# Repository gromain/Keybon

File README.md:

# Keybon - Adaptive Macro Keyboard

Keybon is a macro keyboard with configurable layouts and functions. Integrated into each of its nine tactile buttons is a 0.66” OLED screen. Depending on which app is active on the connected computer, Keybon switches to the suitable key layout thanks to its companion software.

This repository also contains a 12 buttons version called Keybon12. The corresponding files and code were designed by Romain Bazile. It's built upon the work of [CoretechR](https://github.com/CoretechR/Keybon/).

# Instructions

1.  Download the USB bootloader: https://github.com/rogerclarkmelbourne/STM32duino-bootloader

    Connect a USB-to-Serial adapter to the TX/RX pins of your board. Close the BOOT0 jumper before applying power.

    Locate the file to flash, in the folder `bootloader_only_binaries/generic_boot20_pc13.bin`.

    Flash the USB bootloader to the STM32 via the STM32 flasher:  https://www.st.com/en/development-tools/flasher-stm32.html

    You can also use the `stm32loader.py` script provided by `STM32duino-bootloader` team.

    Do not forget to remove the BOOT0 jumper once you're done.

2.  Install the required Arduino libraries listed in the `keybon12.ino` file

    Important: **Adafruit_GFX_Library version 1.7.5** must be installed (dependencies for newer versions are incompatible with the STM32)

    Add these lines to the file `Adafruit_SSD1306.c` (in `Arduino/libraries/Adafruit_SSD1306`)
    
    ```C++
    } else if ((WIDTH == 128) && (HEIGHT == 48)) {
    comPins = 0x12;
	  contrast = (vccstate == SSD1306_EXTERNALVCC) ? 0x9F : 0xCF;
    ```

    They should be added around line 563, right after this:
    ```C++
    } else if ((WIDTH == 96) && (HEIGHT == 16)) {
    comPins = 0x2; // ada x12
    contrast = (vccstate == SSD1306_EXTERNALVCC) ? 0x10 : 0xAF;
    ```

3.  Install STM32 support for the Arduino IDE: https://github.com/rogerclarkmelbourne/Arduino_STM32

    Install the corresponding drivers: https://github.com/rogerclarkmelbourne/Arduino_STM32/tree/master/drivers

4.  Compile and upload the Arduino sketch:

    The first time you do this, you will need to short the BOOT1 jumper and then restart your Keybon (either by plugging it in, or by clicking on the reset button).

    If you are using Linux, you may need to add a udev rule to your system (or to use `sudo` with the last command executed by the Arduino IDE).

    If you need to create new icons for your display, you can use the tool at https://javl.github.io/image2cpp/ with png images, in black and white only and a resolution of 64*48 pixels.

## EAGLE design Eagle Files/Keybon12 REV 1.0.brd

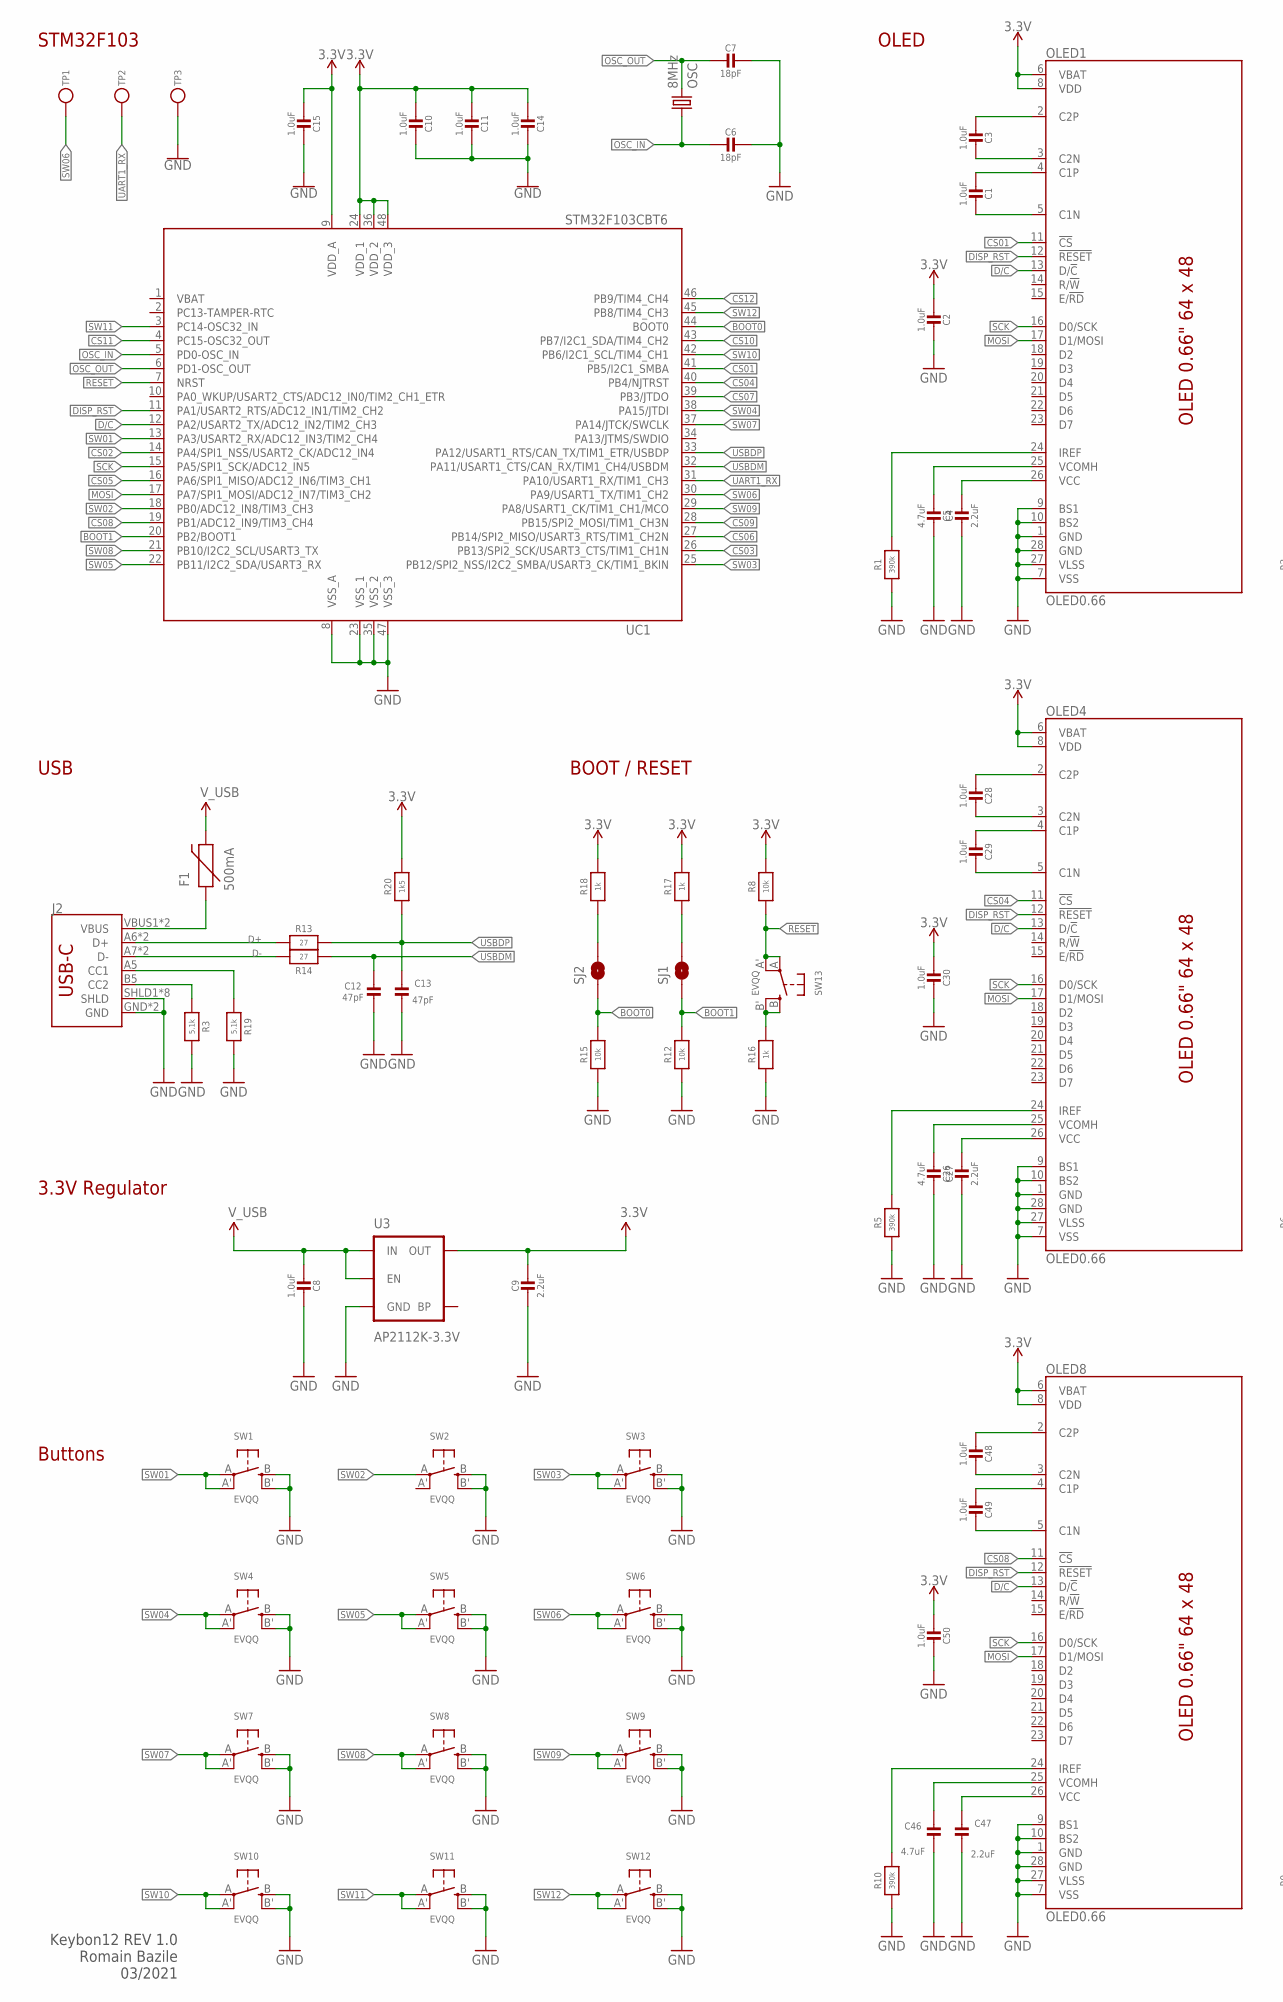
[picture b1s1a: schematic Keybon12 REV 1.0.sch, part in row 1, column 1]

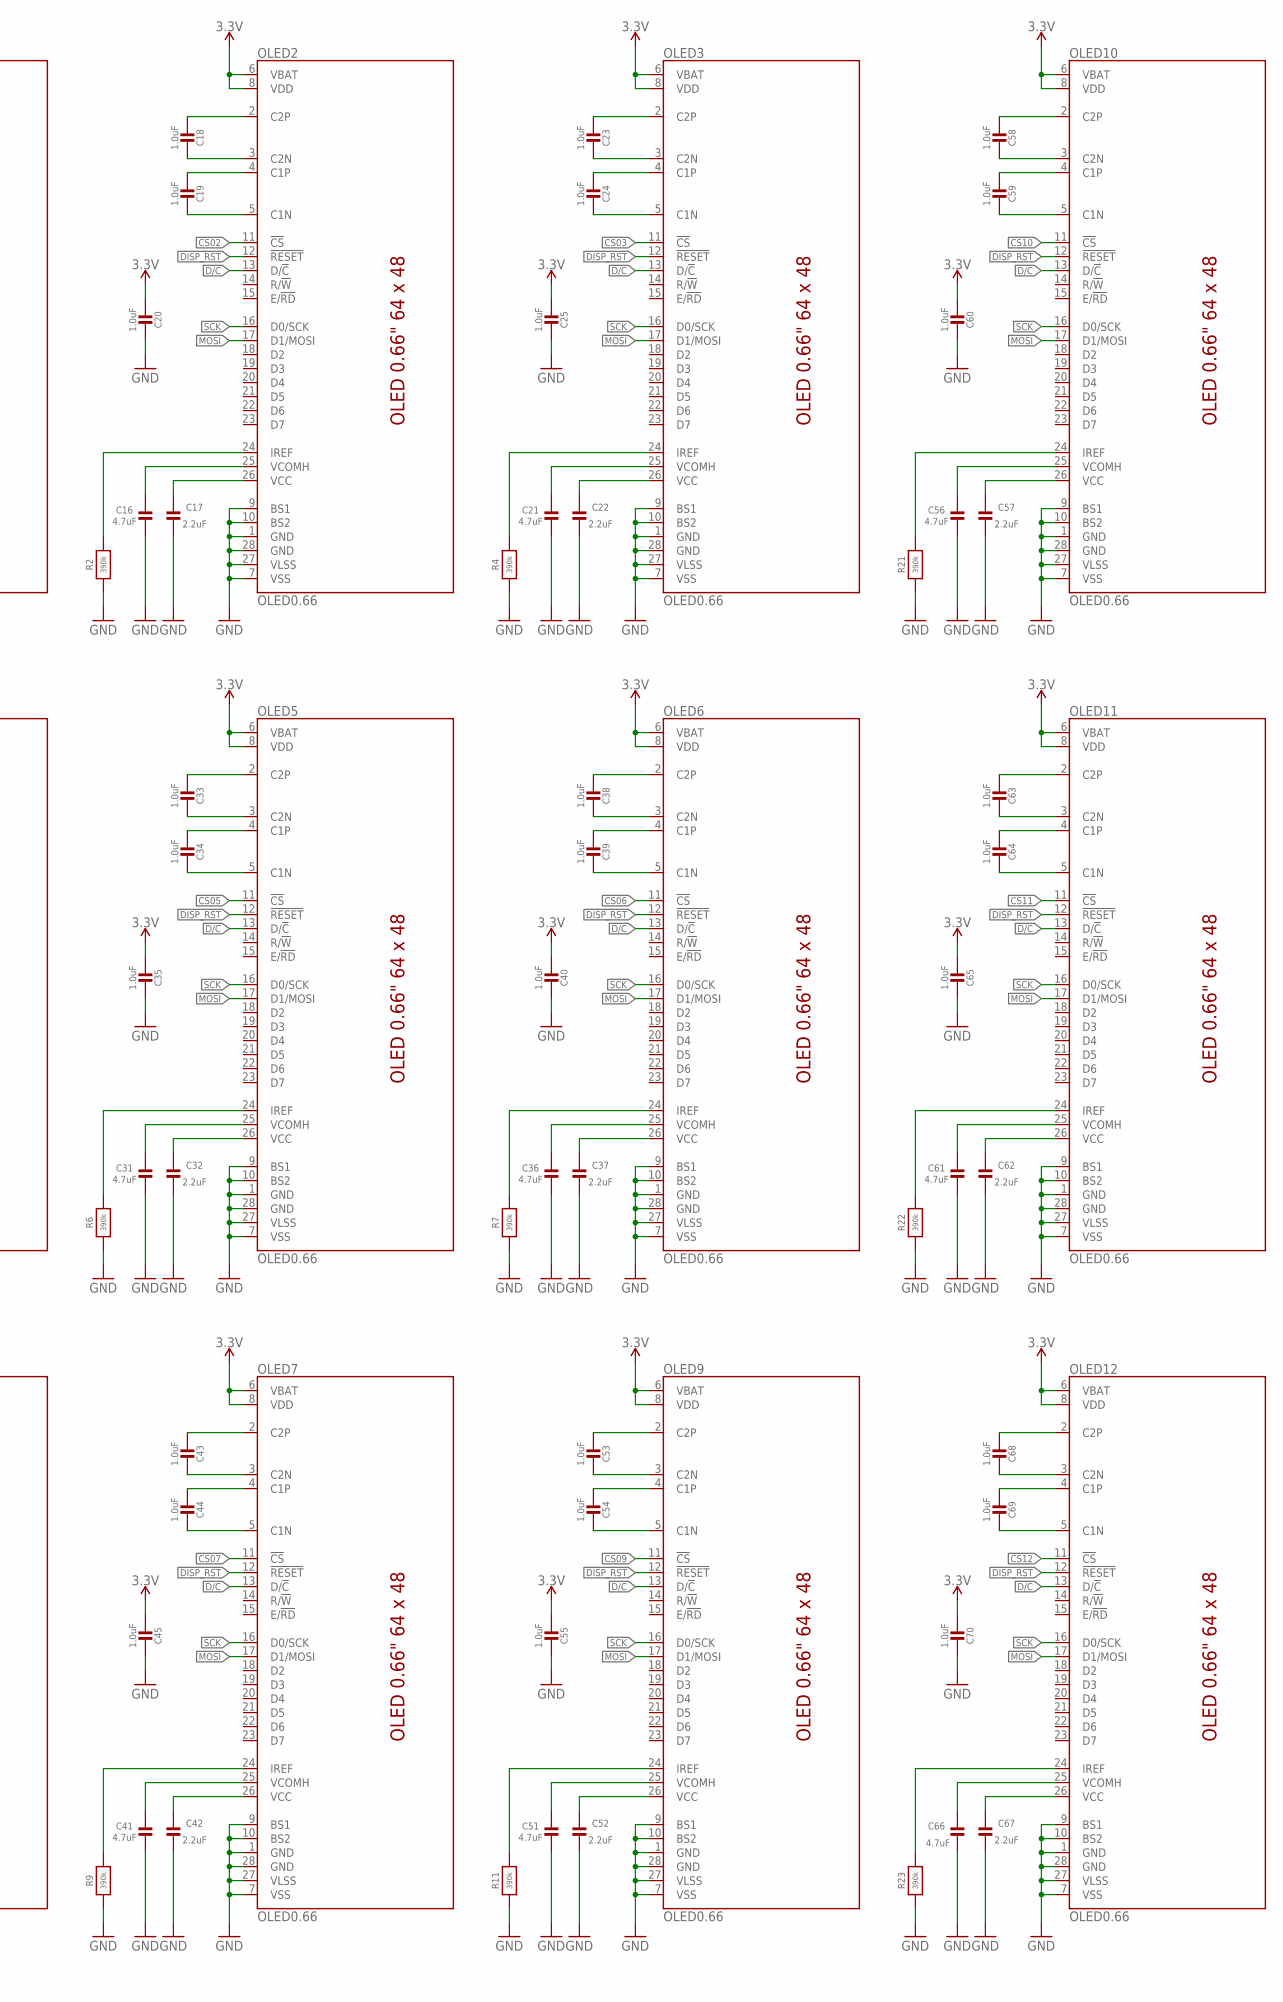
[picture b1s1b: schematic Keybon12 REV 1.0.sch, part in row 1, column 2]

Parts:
C1, C2, C3, C8, C10, C11, C14, C15, C18, C19, C20, C23, C24, C25, C28, C29, C30, C33, C34, C35, C38, C39, C40, C43, C44, C45, C48, C49, C50, C53, C54, C55, C58, C59, C60, C63, C64, C65, C68, C69, C70: 1.0uF; _0805MP
C4, C9, C17, C22, C27, C32, C37, C42, C47, C52, C57, C62, C67: 2.2uF; _0805MP
C5, C16, C21, C26, C31, C36, C41, C46, C51, C56, C61, C66: 4.7uF; _0805MP
C6, C7: 18pF; _0805MP
C12, C13: 47pF; _0805MP
F1: 500mA; PTC-1206
J2: USB_C16PIN; USB-C-16P
OLED1, OLED2, OLED3, OLED4, OLED5, OLED6, OLED7, OLED8, OLED9, OLED10, OLED11, OLED12: OLED0.66; OLED-0.66-64X48
OSC: 8MHz; CRYSTAL-SMD-5X3
R1, R2, R4, R5, R6, R7, R9, R10, R11, R21, R22, R23: 390k; _0805MP
R3, R19: 5.1k; _0805MP
R8, R12, R15: 10k; _0805MP
R13, R14: 27; _0805MP
R16, R17, R18: 1k; _0805MP
R20: 1k5; _0805MP
SJ1, SJ2: JUMPER-PAD-2-NOYES_SILK; PAD-JUMPER-2-NO_YES_SILK
SW1, SW2, SW3, SW4, SW5, SW6, SW7, SW8, SW9, SW10, SW11, SW12, SW13: EVQQ; EVQ-Q2_SMALLER
TP1, TP2, TP3: TESTPOINTPAD2MM; TESTPOINT_PAD_2MM
U3: AP2112K-3.3V; SOT23-5
UC1: STM32F103CBT6; LQFP48

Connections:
3.3V: C2.1, C9.1, C10.1, C11.1, C14.1, C15.1, C20.1, C25.1, C30.1, C35.1, C40.1, C45.1, C50.1, C55.1, C60.1, C65.1, C70.1, OLED1.6 (VBAT), OLED1.8 (VDD), OLED2.6 (VBAT), OLED2.8 (VDD), OLED3.6 (VBAT), OLED3.8 (VDD), OLED4.6 (VBAT), OLED4.8 (VDD), OLED5.6 (VBAT), OLED5.8 (VDD), OLED6.6 (VBAT), OLED6.8 (VDD), OLED7.6 (VBAT), OLED7.8 (VDD), OLED8.6 (VBAT), OLED8.8 (VDD), OLED9.6 (VBAT), OLED9.8 (VDD), OLED10.6 (VBAT), OLED10.8 (VDD), OLED11.6 (VBAT), OLED11.8 (VDD), OLED12.6 (VBAT), OLED12.8 (VDD), R8.2, R17.2, R18.2, R20.2, U3.5 (OUT), UC1.9 (VDD_A), UC1.24 (VDD_1), UC1.36 (VDD_2), UC1.48 (VDD_3)
BOOT0: R15.2, SJ2.1, UC1.44 (BOOT0)
BOOT1: R12.2, SJ1.1, UC1.20 (PB2/BOOT1)
C1N: C1.2, OLED1.5 (C1N)
C1N1: C19.2, OLED2.5 (C1N)
C1N2: C24.2, OLED3.5 (C1N)
C1N3: C29.2, OLED4.5 (C1N)
C1N4: C34.2, OLED5.5 (C1N)
C1N5: C39.2, OLED6.5 (C1N)
C1N6: C44.2, OLED7.5 (C1N)
C1N7: C49.2, OLED8.5 (C1N)
C1N8: C54.2, OLED9.5 (C1N)
C1N9: C59.2, OLED10.5 (C1N)
C1N10: C64.2, OLED11.5 (C1N)
C1N11: C69.2, OLED12.5 (C1N)
C1P: C1.1, OLED1.4 (C1P)
C1P1: C19.1, OLED2.4 (C1P)
C1P2: C24.1, OLED3.4 (C1P)
C1P3: C29.1, OLED4.4 (C1P)
C1P4: C34.1, OLED5.4 (C1P)
C1P5: C39.1, OLED6.4 (C1P)
C1P6: C44.1, OLED7.4 (C1P)
C1P7: C49.1, OLED8.4 (C1P)
C1P8: C54.1, OLED9.4 (C1P)
C1P9: C59.1, OLED10.4 (C1P)
C1P10: C64.1, OLED11.4 (C1P)
C1P11: C69.1, OLED12.4 (C1P)
C2N: C3.2, OLED1.3 (C2N)
C2N1: C18.2, OLED2.3 (C2N)
C2N2: C23.2, OLED3.3 (C2N)
C2N3: C28.2, OLED4.3 (C2N)
C2N4: C33.2, OLED5.3 (C2N)
C2N5: C38.2, OLED6.3 (C2N)
C2N6: C43.2, OLED7.3 (C2N)
C2N7: C48.2, OLED8.3 (C2N)
C2N8: C53.2, OLED9.3 (C2N)
C2N9: C58.2, OLED10.3 (C2N)
C2N10: C63.2, OLED11.3 (C2N)
C2N11: C68.2, OLED12.3 (C2N)
C2P: C3.1, OLED1.2 (C2P)
C2P1: C18.1, OLED2.2 (C2P)
C2P2: C23.1, OLED3.2 (C2P)
C2P3: C28.1, OLED4.2 (C2P)
C2P4: C33.1, OLED5.2 (C2P)
C2P5: C38.1, OLED6.2 (C2P)
C2P6: C43.1, OLED7.2 (C2P)
C2P7: C48.1, OLED8.2 (C2P)
C2P8: C53.1, OLED9.2 (C2P)
C2P9: C58.1, OLED10.2 (C2P)
C2P10: C63.1, OLED11.2 (C2P)
C2P11: C68.1, OLED12.2 (C2P)
CS01: OLED1.11 (!CS!), UC1.41 (PB5/I2C1_SMBA)
CS02: OLED2.11 (!CS!), UC1.14 (PA4/SPI1_NSS/USART2_CK/ADC12_IN4)
CS03: OLED3.11 (!CS!), UC1.26 (PB13/SPI2_SCK/USART3_CTS/TIM1_CH1N)
CS04: OLED4.11 (!CS!), UC1.40 (PB4/NJTRST)
CS05: OLED5.11 (!CS!), UC1.16 (PA6/SPI1_MISO/ADC12_IN6/TIM3_CH1)
CS06: OLED6.11 (!CS!), UC1.27 (PB14/SPI2_MISO/USART3_RTS/TIM1_CH2N)
CS07: OLED7.11 (!CS!), UC1.39 (PB3/JTDO)
CS08: OLED8.11 (!CS!), UC1.19 (PB1/ADC12_IN9/TIM3_CH4)
CS09: OLED9.11 (!CS!), UC1.28 (PB15/SPI2_MOSI/TIM1_CH3N)
CS10: OLED10.11 (!CS!), UC1.43 (PB7/I2C1_SDA/TIM4_CH2)
CS11: OLED11.11 (!CS!), UC1.4 (PC15-OSC32_OUT)
CS12: OLED12.11 (!CS!), UC1.46 (PB9/TIM4_CH4)
D+: J2.A6 (D+), J2.B6 (D+), R13.1
D-: J2.A7 (D-), J2.B7 (D-), R14.1
D/C: OLED1.13 (D/!C!), OLED2.13 (D/!C!), OLED3.13 (D/!C!), OLED4.13 (D/!C!), OLED5.13 (D/!C!), OLED6.13 (D/!C!), OLED7.13 (D/!C!), OLED8.13 (D/!C!), OLED9.13 (D/!C!), OLED10.13 (D/!C!), OLED11.13 (D/!C!), OLED12.13 (D/!C!), UC1.12 (PA2/USART2_TX/ADC12_IN2/TIM2_CH3)
DISP_RST: OLED1.12 (!RESET!), OLED2.12 (!RESET!), OLED3.12 (!RESET!), OLED4.12 (!RESET!), OLED5.12 (!RESET!), OLED6.12 (!RESET!), OLED7.12 (!RESET!), OLED8.12 (!RESET!), OLED9.12 (!RESET!), OLED10.12 (!RESET!), OLED11.12 (!RESET!), OLED12.12 (!RESET!), UC1.11 (PA1/USART2_RTS/ADC12_IN1/TIM2_CH2)
GND: C2.2, C4.2, C5.2, C6.1, C7.1, C8.2, C9.2, C10.2, C11.2, C12.2, C13.2, C14.2, C15.2, C16.2, C17.2, C20.2, C21.2, C22.2, C25.2, C26.2, C27.2, C30.2, C31.2, C32.2, C35.2, C36.2, C37.2, C40.2, C41.2, C42.2, C45.2, C46.2, C47.2, C50.2, C51.2, C52.2, C55.2, C56.2, C57.2, C60.2, C61.2, C62.2, C65.2, C66.2, C67.2, C70.2, J2.GND, J2.GND2 (GND), J2.SHLD1 (SHLD), J2.SHLD2 (SHLD), J2.SHLD3 (SHLD), J2.SHLD4 (SHLD), J2.SHLD5 (SHLD), J2.SHLD6 (SHLD), J2.SHLD7 (SHLD), J2.SHLD8 (SHLD), OLED1.1 (GND), OLED1.7 (VSS), OLED1.9 (BS1), OLED1.10 (BS2), OLED1.27 (VLSS), OLED1.28 (GND), OLED2.1 (GND), OLED2.7 (VSS), OLED2.9 (BS1), OLED2.10 (BS2), OLED2.27 (VLSS), OLED2.28 (GND), OLED3.1 (GND), OLED3.7 (VSS), OLED3.9 (BS1), OLED3.10 (BS2), OLED3.27 (VLSS), OLED3.28 (GND), OLED4.1 (GND), OLED4.7 (VSS), OLED4.9 (BS1), OLED4.10 (BS2), OLED4.27 (VLSS), OLED4.28 (GND), OLED5.1 (GND), OLED5.7 (VSS), OLED5.9 (BS1), OLED5.10 (BS2), OLED5.27 (VLSS), OLED5.28 (GND), OLED6.1 (GND), OLED6.7 (VSS), OLED6.9 (BS1), OLED6.10 (BS2), OLED6.27 (VLSS), OLED6.28 (GND), OLED7.1 (GND), OLED7.7 (VSS), OLED7.9 (BS1), OLED7.10 (BS2), OLED7.27 (VLSS), OLED7.28 (GND), OLED8.1 (GND), OLED8.7 (VSS), OLED8.9 (BS1), OLED8.10 (BS2), OLED8.27 (VLSS), OLED8.28 (GND), OLED9.1 (GND), OLED9.7 (VSS), OLED9.9 (BS1), OLED9.10 (BS2), OLED9.27 (VLSS), OLED9.28 (GND), OLED10.1 (GND), OLED10.7 (VSS), OLED10.9 (BS1), OLED10.10 (BS2), OLED10.27 (VLSS), OLED10.28 (GND), OLED11.1 (GND), OLED11.7 (VSS), OLED11.9 (BS1), OLED11.10 (BS2), OLED11.27 (VLSS), OLED11.28 (GND), OLED12.1 (GND), OLED12.7 (VSS), OLED12.9 (BS1), OLED12.10 (BS2), OLED12.27 (VLSS), OLED12.28 (GND), R1.2, R2.2, R3.2, R4.2, R5.2, R6.2, R7.2, R9.2, R10.2, R11.2, R12.1, R15.1, R16.1, R19.2, R21.2, R22.2, R23.2, SW1.B (S), SW1.B' (S1), SW2.B (S), SW2.B' (S1), SW3.B (S), SW3.B' (S1), SW4.B (S), SW4.B' (S1), SW5.B (S), SW5.B' (S1), SW6.B (S), SW6.B' (S1), SW7.B (S), SW7.B' (S1), SW8.B (S), SW8.B' (S1), SW9.B (S), SW9.B' (S1), SW10.B (S), SW10.B' (S1), SW11.B (S), SW11.B' (S1), SW12.B (S), SW12.B' (S1), TP3.P$1, U3.2 (GND), UC1.8 (VSS_A), UC1.23 (VSS_1), UC1.35 (VSS_2), UC1.47 (VSS_3)
IREF: OLED1.24 (IREF), R1.1
IREF1: OLED2.24 (IREF), R2.1
IREF2: OLED3.24 (IREF), R4.1
IREF3: OLED4.24 (IREF), R5.1
IREF4: OLED5.24 (IREF), R6.1
IREF5: OLED6.24 (IREF), R7.1
IREF6: OLED7.24 (IREF), R9.1
IREF7: OLED8.24 (IREF), R10.1
IREF8: OLED9.24 (IREF), R11.1
IREF9: OLED10.24 (IREF), R21.1
IREF10: OLED11.24 (IREF), R22.1
IREF11: OLED12.24 (IREF), R23.1
MOSI: OLED1.17 (D1/MOSI), OLED2.17 (D1/MOSI), OLED3.17 (D1/MOSI), OLED4.17 (D1/MOSI), OLED5.17 (D1/MOSI), OLED6.17 (D1/MOSI), OLED7.17 (D1/MOSI), OLED8.17 (D1/MOSI), OLED9.17 (D1/MOSI), OLED10.17 (D1/MOSI), OLED11.17 (D1/MOSI), OLED12.17 (D1/MOSI), UC1.17 (PA7/SPI1_MOSI/ADC12_IN7/TIM3_CH2)
unnamed: R16.2, SW13.B (S), SW13.B' (S1)
unnamed: R18.1, SJ2.2
unnamed: R17.1, SJ1.2
unnamed: C4.1, OLED1.26 (VCC)
unnamed: C17.1, OLED2.26 (VCC)
unnamed: C22.1, OLED3.26 (VCC)
unnamed: C37.1, OLED6.26 (VCC)
unnamed: C32.1, OLED5.26 (VCC)
unnamed: J2.A5 (CC1), R19.1
unnamed: C27.1, OLED4.26 (VCC)
unnamed: J2.B5 (CC2), R3.1
unnamed: C47.1, OLED8.26 (VCC)
unnamed: C42.1, OLED7.26 (VCC)
unnamed: C52.1, OLED9.26 (VCC)
unnamed: C57.1, OLED10.26 (VCC)
unnamed: C62.1, OLED11.26 (VCC)
unnamed: C67.1, OLED12.26 (VCC)
OSC_IN: C6.2, OSC.1, UC1.5 (PD0-OSC_IN)
OSC_OUT: C7.2, OSC.3 (2), UC1.6 (PD1-OSC_OUT)
RESET: R8.1, SW13.A, SW13.A' (P1), UC1.7 (NRST)
SCK: OLED1.16 (D0/SCK), OLED2.16 (D0/SCK), OLED3.16 (D0/SCK), OLED4.16 (D0/SCK), OLED5.16 (D0/SCK), OLED6.16 (D0/SCK), OLED7.16 (D0/SCK), OLED8.16 (D0/SCK), OLED9.16 (D0/SCK), OLED10.16 (D0/SCK), OLED11.16 (D0/SCK), OLED12.16 (D0/SCK), UC1.15 (PA5/SPI1_SCK/ADC12_IN5)
SW01: SW1.A, SW1.A' (P1), UC1.13 (PA3/USART2_RX/ADC12_IN3/TIM2_CH4)
SW02: SW2.A, UC1.18 (PB0/ADC12_IN8/TIM3_CH3)
SW03: SW3.A, SW3.A' (P1), UC1.25 (PB12/SPI2_NSS/I2C2_SMBA/USART3_CK/TIM1_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)
SW04: SW4.A, SW4.A' (P1), UC1.38 (PA15/JTDI)
SW05: SW5.A, SW5.A' (P1), UC1.22 (PB11/I2C2_SDA/USART3_RX)
SW06: SW6.A, SW6.A' (P1), TP1.P$1, UC1.30 (PA9/USART1_TX/TIM1_CH2)
SW07: SW7.A, SW7.A' (P1), UC1.37 (PA14/JTCK/SWCLK)
SW08: SW8.A, SW8.A' (P1), UC1.21 (PB10/I2C2_SCL/USART3_TX)
SW09: SW9.A, SW9.A' (P1), UC1.29 (PA8/USART1_CK/TIM1_CH1/MCO)
SW10: SW10.A, SW10.A' (P1), UC1.42 (PB6/I2C1_SCL/TIM4_CH1)
SW11: SW11.A, SW11.A' (P1), UC1.3 (PC14-OSC32_IN)
SW12: SW12.A, SW12.A' (P1), UC1.45 (PB8/TIM4_CH3)
UART1_RX: TP2.P$1, UC1.31 (PA10/USART1_RX/TIM1_CH3)
USBDM: C12.1, R14.2, UC1.32 (PA11/USART1_CTS/CAN_RX/TIM1_CH4/USBDM)
USBDP: C13.1, R13.2, R20.1, UC1.33 (PA12/USART1_RTS/CAN_TX/TIM1_ETR/USBDP)
VBAT: UC1.1 (VBAT)
VCOMH: C5.1, OLED1.25 (VCOMH)
VCOMH1: C16.1, OLED2.25 (VCOMH)
VCOMH2: C21.1, OLED3.25 (VCOMH)
VCOMH3: C26.1, OLED4.25 (VCOMH)
VCOMH4: C31.1, OLED5.25 (VCOMH)
VCOMH5: C36.1, OLED6.25 (VCOMH)
VCOMH6: C41.1, OLED7.25 (VCOMH)
VCOMH7: C46.1, OLED8.25 (VCOMH)
VCOMH8: C51.1, OLED9.25 (VCOMH)
VCOMH9: C56.1, OLED10.25 (VCOMH)
VCOMH10: C61.1, OLED11.25 (VCOMH)
VCOMH11: C66.1, OLED12.25 (VCOMH)
VUSB-RAW: F1.1, J2.VBUS1 (VBUS), J2.VBUS2 (VBUS)
V_USB: C8.1, F1.2, U3.1 (IN), U3.3 (EN)

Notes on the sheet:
Buttons
OLED
STM32F103
USB
BOOT / RESET
3.3V Regulator
Keybon12 REV 1.0 Romain Bazile 03/2021

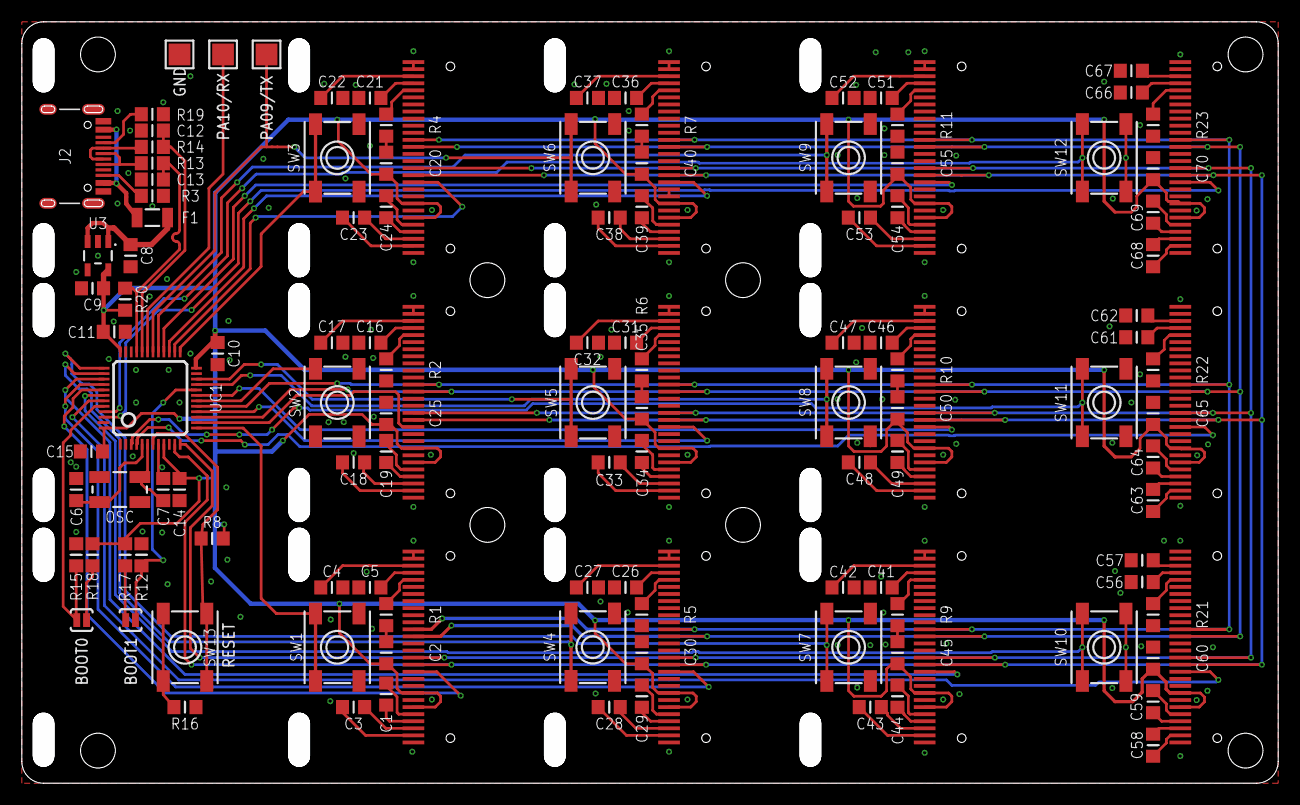
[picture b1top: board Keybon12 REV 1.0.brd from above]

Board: 2 copper layers, 115.5 x 70.0 mm, 128 parts (0 on the bottom side), 131 nets.

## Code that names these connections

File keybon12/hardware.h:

#define PRODUCT_ID 0x29

#define SW01 PA3
#define SW02 PB0
#define SW03 PB12
#define SW04 PA15
#define SW05 PB11
#define SW06 PA9
#define SW07 PA14
#define SW08 PB10
#define SW09 PA8
#define SW10 PB6
#define SW11 PC14
#define SW12 PB8

#define OLED_MOSI    PA7
#define OLED_CLK     PA5
#define OLED_DC      PA2
#define OLED_CS01    PB5
#define OLED_CS02    PA4
#define OLED_CS03    PB13
#define OLED_CS04    PB4
#define OLED_CS05    PA6
#define OLED_CS06    PB14
#define OLED_CS07    PB3
#define OLED_CS08    PB1
#define OLED_CS09    PB15
#define OLED_CS10    PB7
#define OLED_CS11    PC15
#define OLED_CS12    PB9
#define OLED_RESET   PA1

Adafruit_SSD1306 OLED01(128, 48, OLED_MOSI, OLED_CLK, OLED_DC, OLED_RESET, OLED_CS01);
Adafruit_SSD1306 OLED02(128, 48, OLED_MOSI, OLED_CLK, OLED_DC, OLED_RESET, OLED_CS02);
Adafruit_SSD1306 OLED03(128, 48, OLED_MOSI, OLED_CLK, OLED_DC, OLED_RESET, OLED_CS03);
Adafruit_SSD1306 OLED04(128, 48, OLED_MOSI, OLED_CLK, OLED_DC, OLED_RESET, OLED_CS04);
Adafruit_SSD1306 OLED05(128, 48, OLED_MOSI, OLED_CLK, OLED_DC, OLED_RESET, OLED_CS05);
Adafruit_SSD1306 OLED06(128, 48, OLED_MOSI, OLED_CLK, OLED_DC, OLED_RESET, OLED_CS06);
Adafruit_SSD1306 OLED07(128, 48, OLED_MOSI, OLED_CLK, OLED_DC, OLED_RESET, OLED_CS07);
Adafruit_SSD1306 OLED08(128, 48, OLED_MOSI, OLED_CLK, OLED_DC, OLED_RESET, OLED_CS08);
Adafruit_SSD1306 OLED09(128, 48, OLED_MOSI, OLED_CLK, OLED_DC, OLED_RESET, OLED_CS09);
Adafruit_SSD1306 OLED10(128, 48, OLED_MOSI, OLED_CLK, OLED_DC, OLED_RESET, OLED_CS10);
Adafruit_SSD1306 OLED11(128, 48, OLED_MOSI, OLED_CLK, OLED_DC, OLED_RESET, OLED_CS11);
Adafruit_SSD1306 OLED12(128, 48, OLED_MOSI, OLED_CLK, OLED_DC, OLED_RESET, OLED_CS12);

Button button01(SW01, 5, true, true); //pin, debounce, pullup, invert
Button button02(SW02, 5, true, true); //pin, debounce, pullup, invert
Button button03(SW03, 5, true, true); //pin, debounce, pullup, invert
Button button04(SW04, 5, true, true); //pin, debounce, pullup, invert
Button button05(SW05, 5, true, true); //pin, debounce, pullup, invert
Button button06(SW06, 5, true, true); //pin, debounce, pullup, invert
Button button07(SW07, 5, true, true); //pin, debounce, pullup, invert
Button button08(SW08, 5, true, true); //pin, debounce, pullup, invert
Button button09(SW09, 5, true, true); //pin, debounce, pullup, invert
Button button10(SW10, 5, true, true); //pin, debounce, pullup, invert
Button button11(SW11, 5, true, true); //pin, debounce, pullup, invert
Button button12(SW12, 5, true, true); //pin, debounce, pullup, invert

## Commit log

2021-03-24 update to keybon.ino for proper compile
2021-03-24 Keybon12 Hardware design files
2021-03-24 Keybon12 Eagle Files and BOM
2021-03-24 Keybon12 source code
2021-03-24 Keybon12: update to Arduino code and README
    This new code architecture should make it easier to both add more
    screens if needed, but also to add more functions, including more
    generic ones.
    While usable, this is still a WIP regarding the architecture.
    Also, this work on Keybon12 is backward compatible with the host
    software developped by CoretechR.
2021-03-24 Keybon12: simplify serial command for screen update
2021-03-24 Keybon12: rewrite serial reception with switch statement
2021-04-23 Keybon12: update arduino code

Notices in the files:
parts and their libraries:
SparkFun-Connectors: Licensing: Creative Commons ShareAlike 4.0 International - https://creativecommons.org/licenses/by-sa/4.0
